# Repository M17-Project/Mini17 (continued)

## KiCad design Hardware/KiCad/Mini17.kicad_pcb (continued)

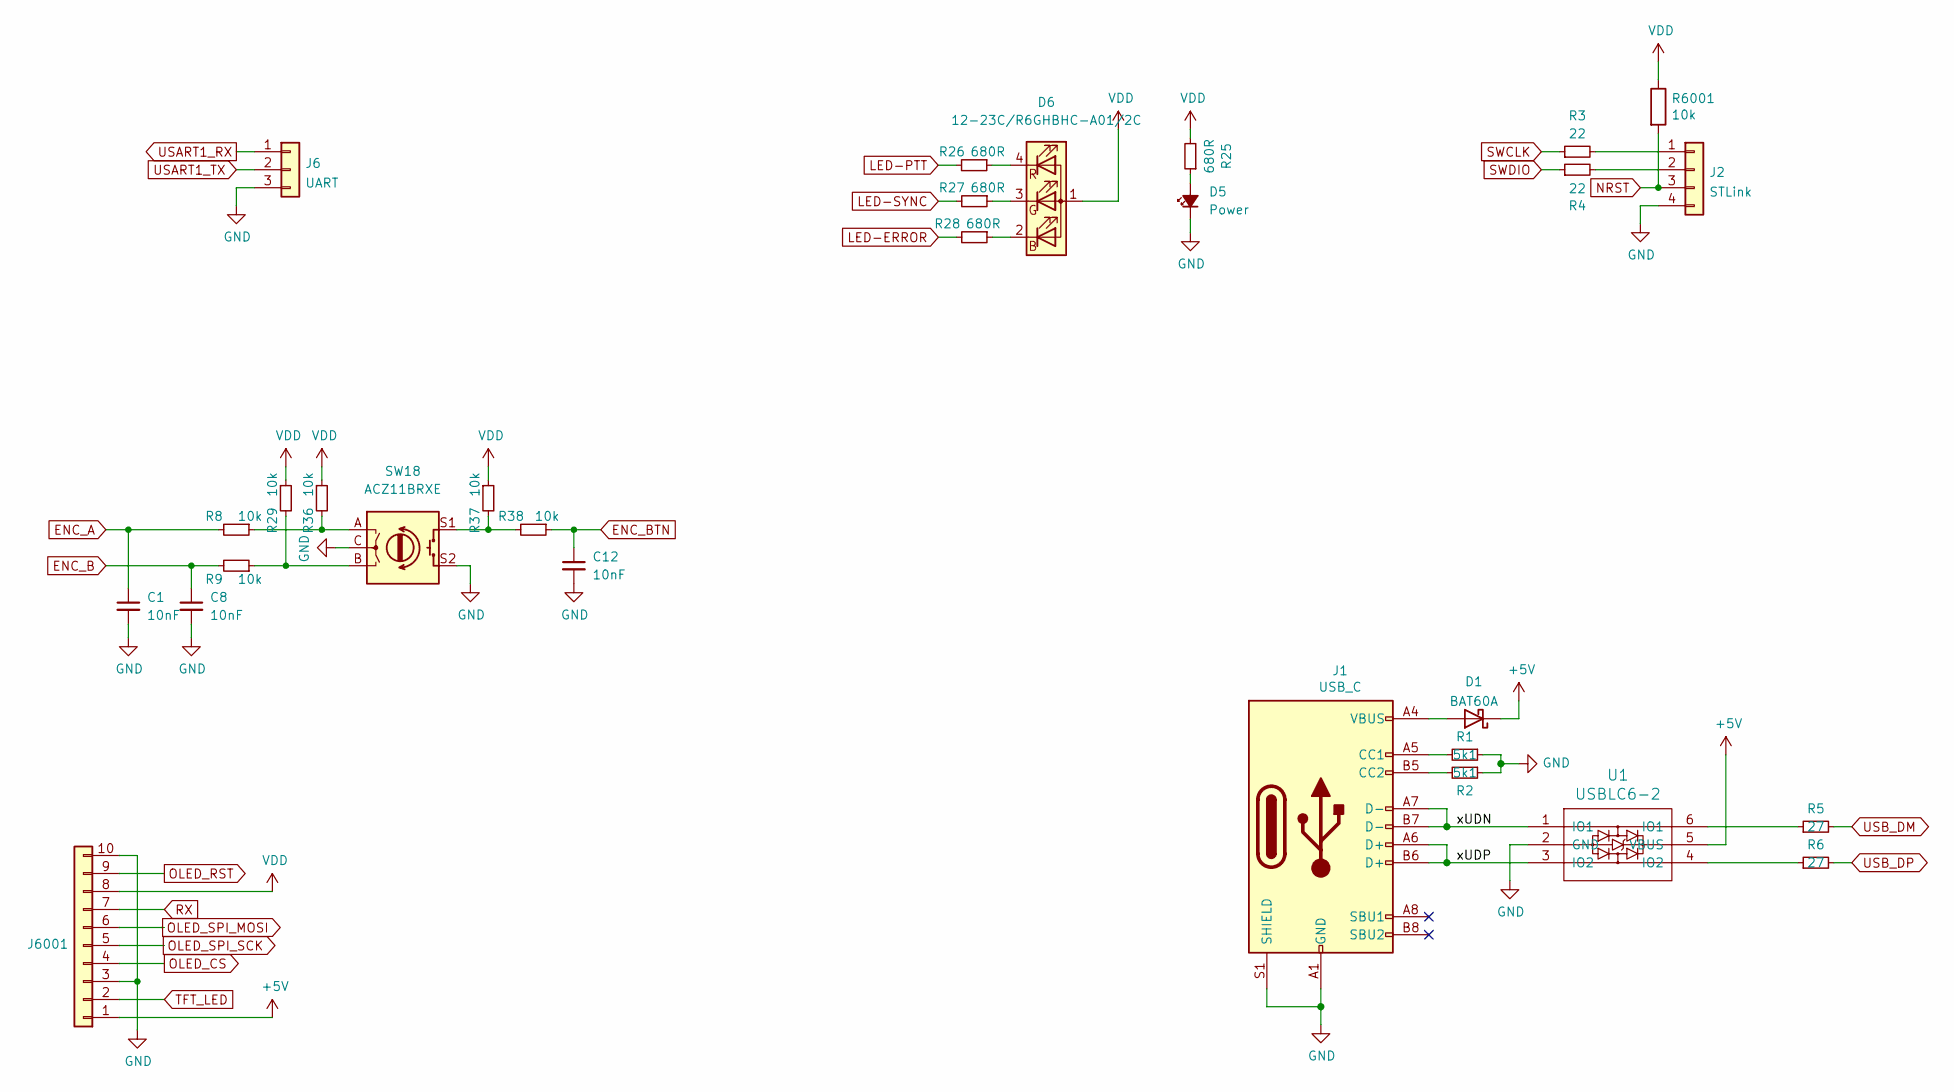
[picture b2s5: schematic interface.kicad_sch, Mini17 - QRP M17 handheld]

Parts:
C1, C8, C12: 10nF; C_0402_1005Metric
D1: BAT60A; D_SOD-323
D5: Power; D_0201_0603Metric
D6: 12-23C/R6GHBHC-A01/2C; LED_RGB_Everlight_EASV3015RGBA0_Horizontal
J1: USB_C; USB_C_Receptacle_GCT_USB4085
J2: STLink; PinHeader_1x04_P2.54mm_Vertical
J6: UART; PinHeader_1x03_P2.54mm_Vertical
J6001: (no value)
R1, R2: 5k1; R_0402_1005Metric
R3, R4: 22; R_0402_1005Metric
R5, R6: 27; R_0402_1005Metric
R8, R9, R29, R36, R37, R38: 10k; R_0402_1005Metric
R25, R26, R27, R28: 680R; R_0402_1005Metric
R6001: 10k; R_0603_1608Metric
SW18: ACZ11BRXE
U1: USBLC6-2; SOT-23-6

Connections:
+5V: D1.1 (K), J6001.1, U1.5 (VBUS); also elsewhere on the board
/Interface/xUDN: J1.A7 (D-), J1.B7 (D-), U1.1 (IO1)
/Interface/xUDP: J1.A6 (D+), J1.B6 (D+), U1.3 (IO2)
ENC_A: C1.1, R8.2; also elsewhere on the board
ENC_B: C8.1, R9.2; also elsewhere on the board
ENC_BTN: C12.1, R38.1; also elsewhere on the board
GND: C1.2, C8.2, C12.2, D5.1 (K), J1.A1 (GND), J1.A12 (GND), J1.B1 (GND), J1.B12 (GND), J1.S1 (SHIELD), J2.4, J6.3, J6001.3, J6001.10, R1.1, R2.1, SW18.C, SW18.S2, U1.2 (GND); also elsewhere on the board
LED-ERROR: R28.2
LED-PTT: R26.2
LED-SYNC: R27.2
NRST: J2.3, R6001.2; also elsewhere on the board
unnamed: D1.2 (A), J1.A4 (VBUS), J1.A9 (VBUS), J1.B4 (VBUS), J1.B9 (VBUS)
unnamed: D5.2 (A), R25.1
unnamed: D6.2 (BK), R28.1
unnamed: D6.3 (GK), R27.1
unnamed: D6.4 (RK), R26.1
unnamed: J1.A5 (CC1), R1.2
unnamed: J1.B5 (CC2), R2.2
unnamed: J2.1, R3.2
unnamed: J2.2, R4.2
unnamed: R5.1, U1.6 (IO1)
unnamed: R6.1, U1.4 (IO2)
unnamed 100: R9.1, R29.2, SW18.B; also elsewhere on the board
unnamed 101: R8.1, R36.2, SW18.A; also elsewhere on the board
unnamed: R37.2, R38.2, SW18.S1
OLED_CS: J6001.4; also elsewhere on the board
OLED_RST: J6001.9; also elsewhere on the board
OLED_SPI_MOSI: J6001.6; also elsewhere on the board
OLED_SPI_SCK: J6001.5; also elsewhere on the board
RX: J6001.7
SWCLK: R3.1; also elsewhere on the board
SWDIO: R4.1; also elsewhere on the board
TFT_LED: J6001.2; also elsewhere on the board
USART1_RX: J6.1; also elsewhere on the board
USART1_TX: J6.2; also elsewhere on the board
USB_DM: R5.2; also elsewhere on the board
USB_DP: R6.2; also elsewhere on the board
VDD: D6.1 (A), J6001.8, R25.2, R29.1, R36.1, R37.1, R6001.1; also elsewhere on the board

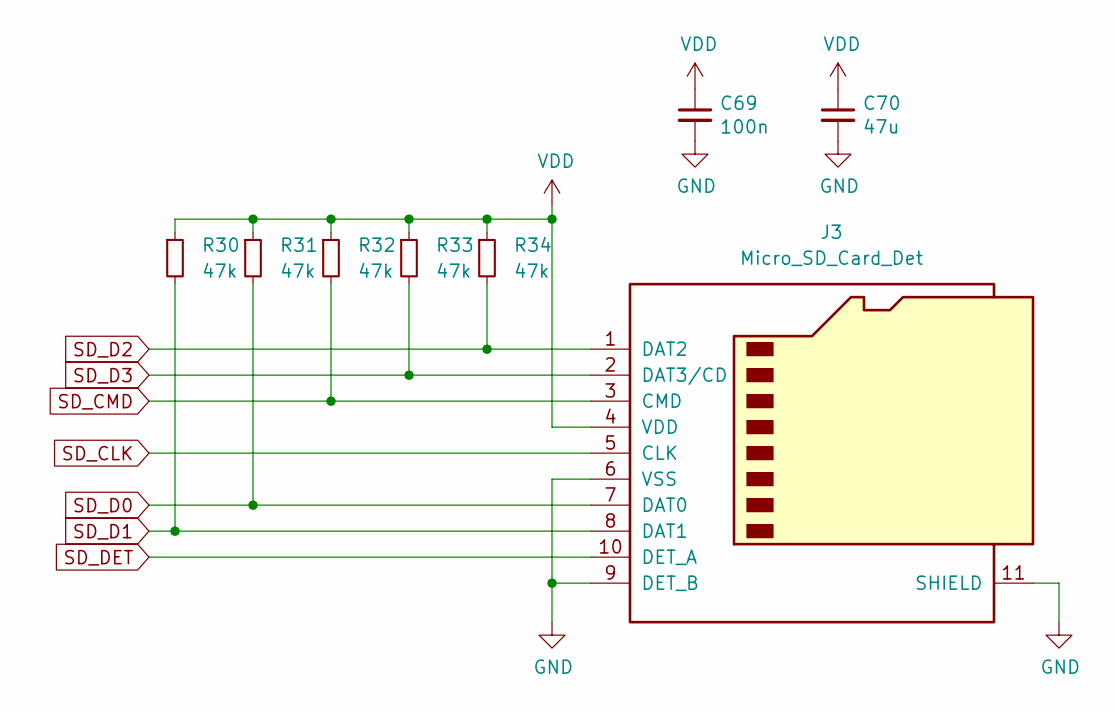
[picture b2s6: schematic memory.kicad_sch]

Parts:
C69: 100n; C_0402_1005Metric
C70: 47u; C_0603
J3: Micro_SD_Card_Det; microSD_HC_Hirose_DM3AT-SF-PEJM5
R30, R31, R32, R33, R34: 47k; R_0402_1005Metric

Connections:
GND: C69.2, C70.2, J3.6 (VSS), J3.9 (DET_B), J3.11 (SHIELD); also elsewhere on the board
SD_CLK: J3.5 (CLK); also elsewhere on the board
SD_CMD: J3.3 (CMD), R32.2; also elsewhere on the board
SD_D0: J3.7 (DAT0), R31.2; also elsewhere on the board
SD_D1: J3.8 (DAT1), R30.2; also elsewhere on the board
SD_D2: J3.1 (DAT2), R34.2; also elsewhere on the board
SD_D3: J3.2 (DAT3/CD), R33.2; also elsewhere on the board
VDD: C69.1, C70.1, J3.4 (VDD), R30.1, R31.1, R32.1, R33.1, R34.1; also elsewhere on the board

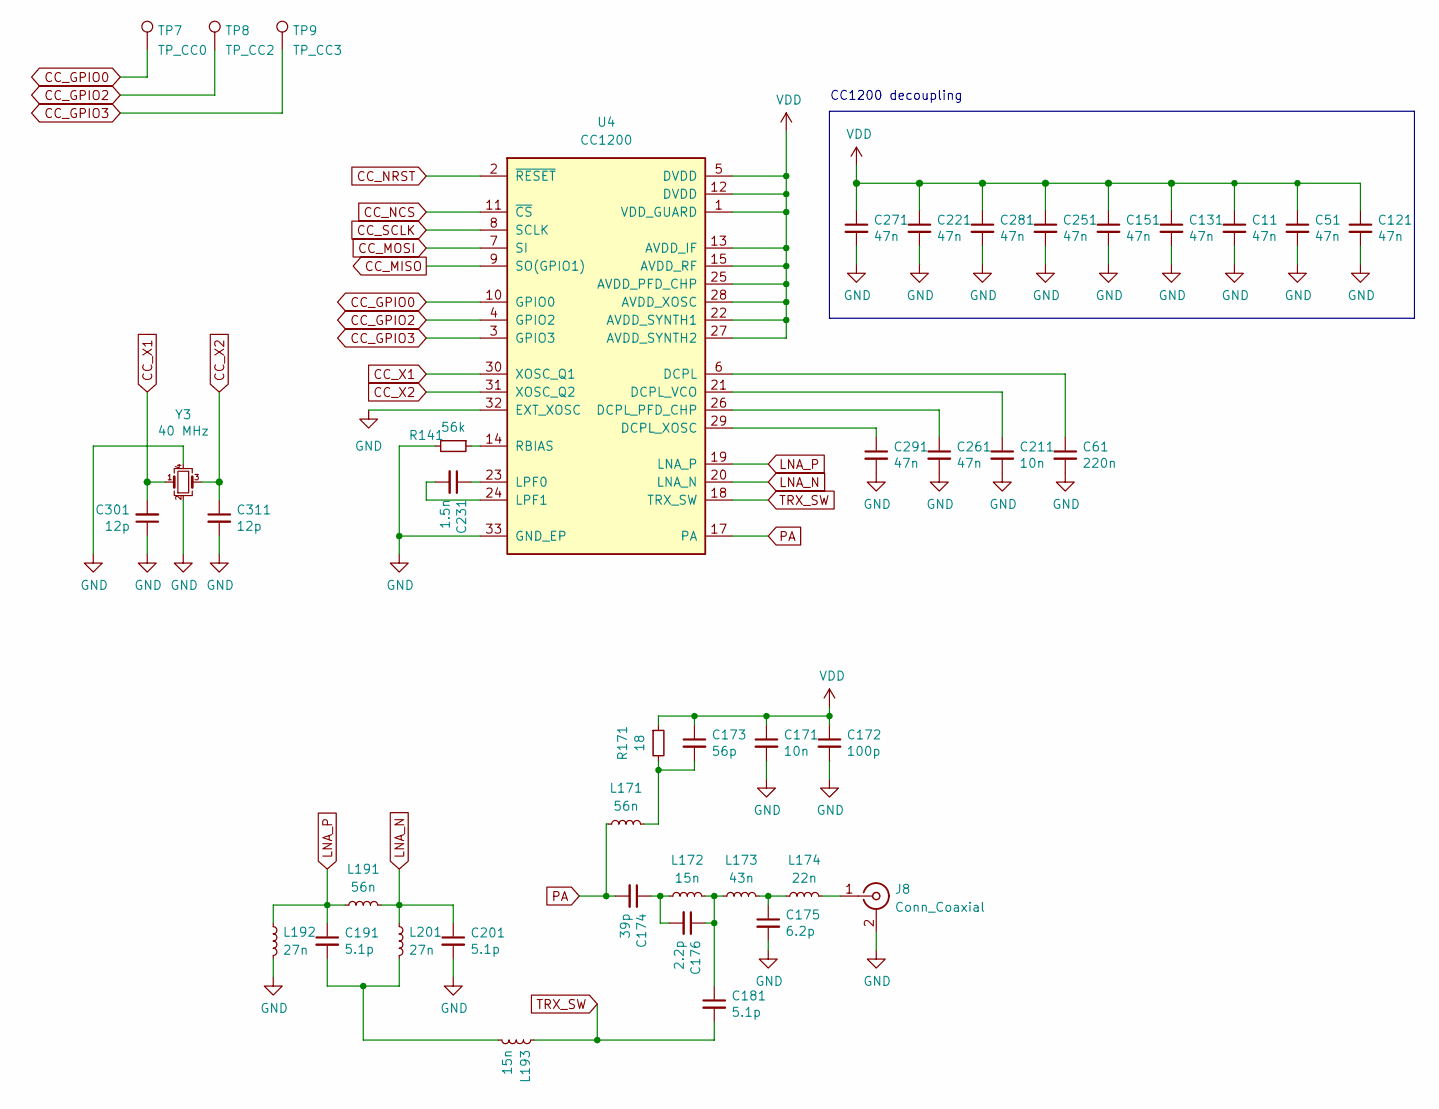
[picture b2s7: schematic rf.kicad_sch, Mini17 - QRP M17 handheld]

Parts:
C11, C51, C121, C131, C151, C221, C251, C261, C271, C281, C291: 47n; C_0402_1005Metric
C61: 220n; C_0402_1005Metric
C171, C211: 10n; C_0402_1005Metric
C172: 100p; C_0402_1005Metric
C173: 56p; C_0402_1005Metric
C174: 39p; C_0402_1005Metric
C175: 6.2p; C_0402_1005Metric
C176: 2.2p; C_0402_1005Metric
C181, C191, C201: 5.1p; C_0402_1005Metric
C231: 1.5n; C_0402_1005Metric
C301, C311: 12p; C_0402_1005Metric
J8: Conn_Coaxial; SMA_Amphenol_901-143_Horizontal
L171, L191: 56n; L_0402_1005Metric
L172, L193: 15n; L_0402_1005Metric
L173: 43n; L_0402_1005Metric
L174: 22n; L_0402_1005Metric
L192, L201: 27n; L_0402_1005Metric
R141: 56k; R_0402_1005Metric
R171: 18; R_0402_1005Metric
TP7: TP_CC0; TestPoint_Pad_D1.0mm
TP8: TP_CC2; TestPoint_Pad_D1.0mm
TP9: TP_CC3; TestPoint_Pad_D1.0mm
U4: CC1200; QFN-32-1EP_5x5mm_P0.5mm_EP3.45x3.45mm
Y3: 40 MHz; Crystal_SMD_3225-4Pin_3.2x2.5mm

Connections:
CC_GPIO0: TP7.1, U4.10 (GPIO0); also elsewhere on the board
CC_GPIO2: TP8.1, U4.4 (GPIO2); also elsewhere on the board
CC_GPIO3: TP9.1, U4.3 (GPIO3); also elsewhere on the board
CC_MISO: U4.9 (SO(GPIO1)); also elsewhere on the board
CC_MOSI: U4.7 (SI); also elsewhere on the board
CC_NCS: U4.11 (~CS); also elsewhere on the board
CC_NRST: U4.2 (~RESET); also elsewhere on the board
CC_SCLK: U4.8 (SCLK); also elsewhere on the board
CC_X1: C301.2, U4.30 (XOSC_Q1), Y3.1
CC_X2: C311.1, U4.31 (XOSC_Q2), Y3.3
GND: C11.2, C51.2, C61.2, C121.2, C131.2, C151.2, C171.2, C172.2, C175.2, C201.2, C211.2, C221.2, C251.2, C261.2, C271.2, C281.2, C291.2, C301.1, C311.2, J8.2 (Ext), L192.2, R141.2, U4.32 (EXT_XOSC), U4.33 (GND_EP), Y3.2, Y3.4; also elsewhere on the board
LNA_N: C201.1, L191.2, L201.1, U4.20 (LNA_N)
LNA_P: C191.1, L191.1, L192.1, U4.19 (LNA_P)
unnamed: C61.1, U4.6 (DCPL)
unnamed: C173.2, L171.2, R171.2
unnamed: C174.1, C176.2, L172.1
unnamed: C175.1, L173.2, L174.1
unnamed: C176.1, C181.1, L172.2, L173.1
unnamed: C191.2, L193.2, L201.2
unnamed: C211.1, U4.21 (DCPL_VCO)
unnamed: C231.1, U4.23 (LPF0)
unnamed: C231.2, U4.24 (LPF1)
unnamed: C261.1, U4.26 (DCPL_PFD_CHP)
unnamed: C291.1, U4.29 (DCPL_XOSC)
unnamed: J8.1 (In), L174.2
unnamed: R141.1, U4.14 (RBIAS)
PA: C174.2, L171.1, U4.17 (PA)
TRX_SW: C181.2, L193.1, U4.18 (TRX_SW)
VDD: C11.1, C51.1, C121.1, C131.1, C151.1, C171.1, C172.1, C173.1, C221.1, C251.1, C271.1, C281.1, R171.1, U4.1 (VDD_GUARD), U4.5 (DVDD), U4.12 (DVDD), U4.13 (AVDD_IF), U4.15 (AVDD_RF), U4.22 (AVDD_SYNTH1), U4.25 (AVDD_PFD_CHP), U4.27 (AVDD_SYNTH2), U4.28 (AVDD_XOSC); also elsewhere on the board

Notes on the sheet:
CC1200 decoupling

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
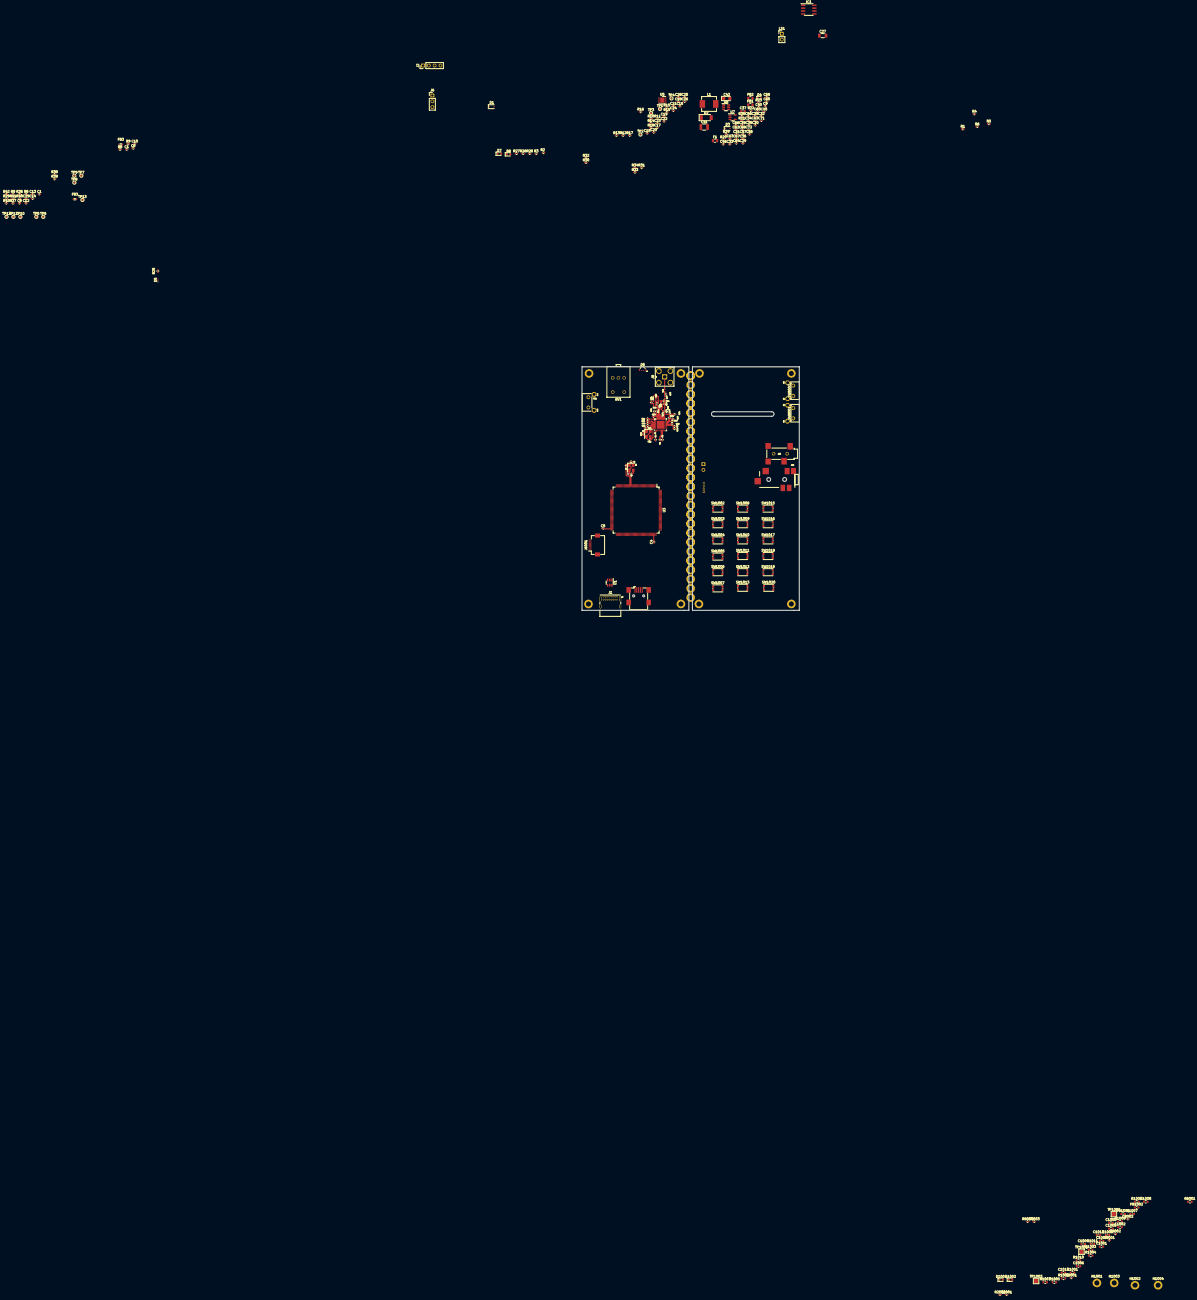
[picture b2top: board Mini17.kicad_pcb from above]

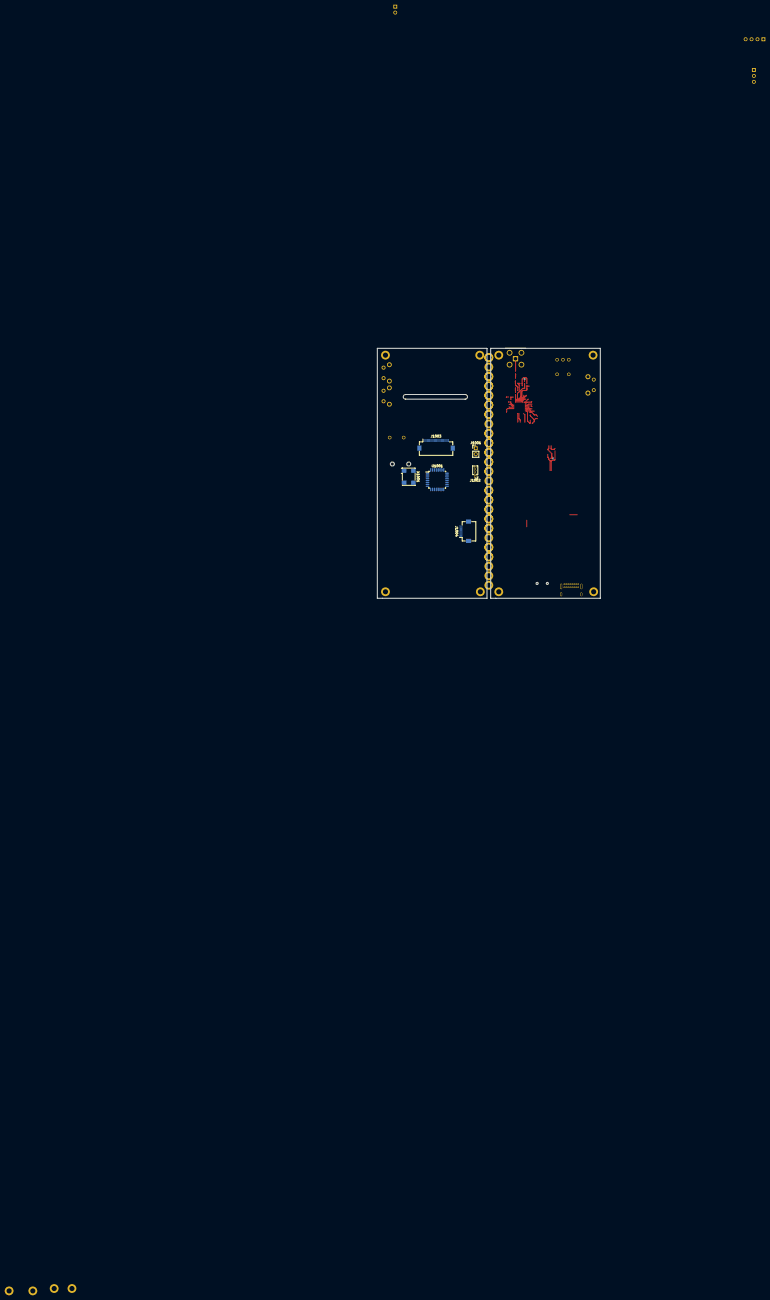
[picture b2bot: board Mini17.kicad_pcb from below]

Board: 4 copper layers, 95.5 x 107.1 mm, 254 parts (6 on the bottom side), 139 nets.

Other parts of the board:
C1#2, C8#2: 10nF; C_0402_1005Metric
C13: 100nF; C_0402_1005Metric
C14, C29: 100n; C_0402_1005Metric
C29#2, C30, C31, C32, C33, C34, C36, C71, C72: 47n; C_0402_1005Metric
D7: Sync; D_0603_1608Metric
D8: Error; D_0603_1608Metric
FB3#2: BLM18AG601SN1D; 0603
J10: MIC_EXT
J12: SPK_EXT
R8#2, R9#2, R40, R41, R42, R43: 10k; R_0402_1005Metric
R39: 47k; R_0402_1005Metric

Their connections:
+5V: J10.1; also elsewhere on the board
BOOT0: C29.1, R43.2; also elsewhere on the board
BTN_F1: C14.1, R41.2; also elsewhere on the board
ENC_A: C1#2.1, R8#2.2; also elsewhere on the board
ENC_B: C8#2.1, R9#2.2; also elsewhere on the board
GND: C1#2.2, C8#2.2, C13.2, C14.2, C29.2, C29#2.2, C30.2, C31.2, C32.2, C33.2, C34.2, C36.2, C71.2, C72.2, J12.2; also elsewhere on the board
MIC: FB3#2.1; also elsewhere on the board
NRST: C13.1, R39.1; also elsewhere on the board
unnamed 85: FB3#2.2; also elsewhere on the board
unnamed 100: R9#2.1; also elsewhere on the board
unnamed 101: R8#2.1; also elsewhere on the board
unnamed: R40.2, R41.1
unnamed: R42.2, R43.1
VDD: C29#2.1, C30.1, C31.1, C32.1, C33.1, C34.1, C36.1, C71.1, C72.1, R40.1, R42.1; also elsewhere on the board

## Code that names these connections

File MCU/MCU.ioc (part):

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Mcu.Name=STM32F427Z(G-I)Tx
Mcu.Package=LQFP144
Mcu.UserName=STM32F427ZGTx
PA0/WKUP.GPIOParameters=GPIO_Label
PA0/WKUP.GPIO_Label=AUDIO_MIC
PA0/WKUP.Signal=ADCx_IN0
PA1.GPIOParameters=GPIO_Label
PA1.GPIO_Label=BAT_MEAS
PA1.Signal=ADCx_IN1
PA10.Mode=Asynchronous
PA10.Signal=USART1_RX
PA11.Mode=Device_Only
PA11.Signal=USB_OTG_FS_DM
PA12.Mode=Device_Only
PA12.Signal=USB_OTG_FS_DP
PA13.Mode=Serial_Wire
PA13.Signal=SYS_JTMS-SWDIO
PA14.Mode=Serial_Wire
PA14.Signal=SYS_JTCK-SWCLK
PA4.GPIOParameters=GPIO_Label
PA4.GPIO_Label=AF_OUT
PA4.Signal=COMP_DAC1_group
PA5.GPIOParameters=GPIO_Label
PA5.GPIO_Label=LED_PTT
PA5.Signal=S_TIM2_CH1_ETR
PA9.Mode=Asynchronous
PA9.Signal=USART1_TX
PB10.GPIOParameters=GPIO_Label
PB10.GPIO_Label=OLED_SPI_SCK
PB10.Mode=TX_Only_Simplex_Unidirect_Master
PB10.Signal=SPI2_SCK
PB11.GPIOParameters=GPIO_Label
PB11.GPIO_Label=OLED_DC
PB11.Signal=GPIO_Output
PB12.GPIOParameters=GPIO_Label
PB12.GPIO_Label=OLED_CS
PB12.Mode=NSS_Signal_Hard_Output
PB12.Signal=SPI2_NSS
PB13.GPIOParameters=GPIO_Label
PB13.GPIO_Label=OLED_RST
PB13.Signal=GPIO_Output
PB15.GPIOParameters=GPIO_Label
PB15.GPIO_Label=OLED_SPI_MOSI
PB15.Mode=TX_Only_Simplex_Unidirect_Master
PB15.Signal=SPI2_MOSI
PC0.GPIOParameters=GPIO_Label
PC0.GPIO_Label=BTN_F1
PC0.Signal=GPXTI0
PC10.Mode=SD_4_bits_Wide_bus
PC10.Signal=SDIO_D2
PC11.Mode=SD_4_bits_Wide_bus
PC11.Signal=SDIO_D3
PC12.Mode=SD_4_bits_Wide_bus
PC12.Signal=SDIO_CK
PC14/OSC32_IN.Mode=LSE-External-Oscillator
PC14/OSC32_IN.Signal=RCC_OSC32_IN
PC15/OSC32_OUT.Mode=LSE-External-Oscillator
PC15/OSC32_OUT.Signal=RCC_OSC32_OUT
PC2.GPIOParameters=GPIO_Label
PC2.GPIO_Label=MIC_GAIN
PC2.Signal=GPIO_Output
PC3.GPIOParameters=GPIO_Label
PC3.GPIO_Label=MIC_MUTE
PC3.Signal=GPIO_Output
PC6.GPIOParameters=GPIO_Label
PC6.GPIO_Label=ENC_B
PC6.Signal=S_TIM8_CH1
PC7.GPIOParameters=GPIO_Label
PC7.GPIO_Label=ENC_A
PC7.Signal=S_TIM8_CH2
PC8.Mode=SD_4_bits_Wide_bus
PC8.Signal=SDIO_D0
PC9.Mode=SD_4_bits_Wide_bus
PC9.Signal=SDIO_D1
PD12.GPIOParameters=GPIO_Label
PD12.GPIO_Label=LED_ERROR
PD12.Signal=S_TIM4_CH1
PD2.Mode=SD_4_bits_Wide_bus
PD2.Signal=SDIO_CMD
PE5.GPIOParameters=GPIO_Label
PE5.GPIO_Label=LED_SYNC
PE5.Signal=S_TIM9_CH1
PE7.GPIOParameters=GPIO_Label
PE7.GPIO_Label=KP_C2
PE7.Signal=GPXTI7
PE8.GPIOParameters=GPIO_Label
PE8.GPIO_Label=KP_C3
PE8.Signal=GPXTI8
PE9.GPIOParameters=GPIO_Label
PE9.GPIO_Label=KP_C4
PE9.Signal=GPXTI9
PF10.GPIOParameters=GPIO_Label
PF10.GPIO_Label=BTN_F2
PF10.Signal=GPXTI10
PF13.GPIOParameters=GPIO_Label
PF13.GPIO_Label=KP_R4
PF13.Signal=GPXTI13
PF14.GPIOParameters=GPIO_Label
PF14.GPIO_Label=KP_R3
PF14.Signal=GPXTI14
PF15.GPIOParameters=GPIO_Label
PF15.GPIO_Label=KP_R2
PF15.Signal=GPXTI15
PF5.GPIOParameters=GPIO_Label
PF5.GPIO_Label=CC_NRST
PF5.Signal=GPIO_Output
PF6.GPIOParameters=GPIO_Label
PF6.GPIO_Label=CC_NSS
PF6.Mode=NSS_Signal_Hard_Output
PF6.Signal=SPI5_NSS
PF7.GPIOParameters=GPIO_Label
PF7.GPIO_Label=CC_SCLK
PF7.Mode=Full_Duplex_Master
PF7.Signal=SPI5_SCK
PF8.GPIOParameters=GPIO_Label
PF8.GPIO_Label=CC_MISO
PF8.Mode=Full_Duplex_Master
PF8.Signal=SPI5_MISO
PF9.GPIOParameters=GPIO_Label
PF9.GPIO_Label=CC_MOSI
PF9.Mode=Full_Duplex_Master
PF9.Signal=SPI5_MOSI
PG1.GPIOParameters=GPIO_Label
PG1.GPIO_Label=KP_C1
PG1.Signal=GPXTI1
PG12.GPIOParameters=GPIO_Label
PG12.GPIO_Label=CC_GPIO3
PG12.Signal=GPXTI12
PH0/OSC_IN.Mode=HSE-External-Oscillator
PH0/OSC_IN.Signal=RCC_OSC_IN
PH1/OSC_OUT.Mode=HSE-External-Oscillator
PH1/OSC_OUT.Signal=RCC_OSC_OUT
RCC.HSE_VALUE=8000000
RCC.SYSCLKFreq_VALUE=108000000
RCC.SYSCLKSource=RCC_SYSCLKSOURCE_PLLCLK
board=custom

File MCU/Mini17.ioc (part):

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Mcu.Name=STM32F405RGTx
Mcu.Package=LQFP64
Mcu.UserName=STM32F405RGTx
PA0-WKUP.GPIOParameters=GPIO_Label
PA0-WKUP.GPIO_Label=AUDIO_MIC
PA0-WKUP.Signal=ADCx_IN0
PA1.GPIOParameters=GPIO_Label
PA1.GPIO_Label=BAT_MEAS
PA1.Signal=ADCx_IN1
PA10.Mode=Asynchronous
PA10.Signal=USART1_RX
PA11.Mode=Device_Only
PA11.Signal=USB_OTG_FS_DM
PA12.Mode=Device_Only
PA12.Signal=USB_OTG_FS_DP
PA13.Mode=Serial_Wire
PA13.Signal=SYS_JTMS-SWDIO
PA14.Mode=Serial_Wire
PA14.Signal=SYS_JTCK-SWCLK
PA2.GPIOParameters=GPIO_Label
PA2.GPIO_Label=TP_B
PA2.Signal=GPIO_Output
PA3.GPIOParameters=GPIO_Label
PA3.GPIO_Label=CC_GPIO0
PA3.Signal=GPIO_Input
PA4.GPIOParameters=GPIO_Label
PA4.GPIO_Label=AF_OUT
PA4.Signal=COMP_DAC1_group
PA5.GPIOParameters=GPIO_Label
PA5.GPIO_Label=CC_GPIO2
PA5.Signal=GPIO_Input
PA6.GPIOParameters=GPIO_Label
PA6.GPIO_Label=LED_R
PA6.Signal=S_TIM3_CH1
PA7.GPIOParameters=GPIO_Label
PA7.GPIO_Label=LED_G
PA7.Signal=S_TIM3_CH2
PA9.Mode=Asynchronous
PA9.Signal=USART1_TX
PB0.GPIOParameters=GPIO_Label
PB0.GPIO_Label=LED_B
PB0.Signal=S_TIM3_CH3
PB1.GPIOParameters=GPIO_Label
PB1.GPIO_Label=CC_GPIO3
PB1.Signal=GPIO_Input
PB10.Mode=Full_Duplex_Master
PB10.Signal=SPI2_SCK
PB11.GPIOParameters=GPIO_Label
PB11.GPIO_Label=OLED_DC
PB11.Signal=GPIO_Output
PB12.GPIOParameters=GPIO_Label
PB12.GPIO_Label=OLED_CS
PB12.Signal=GPIO_Output
PB13.GPIOParameters=GPIO_Label
PB13.GPIO_Label=KBD_CS
PB13.Signal=GPIO_Output
PB14.Mode=Full_Duplex_Master
PB14.Signal=SPI2_MISO
PB15.Mode=Full_Duplex_Master
PB15.Signal=SPI2_MOSI
PB3.Mode=Full_Duplex_Master
PB3.Signal=SPI1_SCK
PB4.Mode=Full_Duplex_Master
PB4.Signal=SPI1_MISO
PB5.Mode=Full_Duplex_Master
PB5.Signal=SPI1_MOSI
PB6.GPIOParameters=GPIO_Label
PB6.GPIO_Label=SPI1_CS
PB6.Signal=GPIO_Output
PB7.GPIOParameters=GPIO_Label
PB7.GPIO_Label=SPI1_RST
PB7.Signal=GPIO_Output
PB8.GPIOParameters=GPIO_Label
PB8.GPIO_Label=MIC_GAIN
PB8.Signal=GPIO_Output
PB9.GPIOParameters=GPIO_Label
PB9.GPIO_Label=MIC_MUTE
PB9.Signal=GPIO_Output
PC0.GPIOParameters=GPIO_Label
PC0.GPIO_Label=PTT_IN
PC0.Signal=GPXTI0
PC1.GPIOParameters=GPIO_Label
PC1.GPIO_Label=BTN_F1
PC1.Signal=GPXTI1
PC10.Mode=SD_4_bits_Wide_bus
PC10.Signal=SDIO_D2
PC11.Mode=SD_4_bits_Wide_bus
PC11.Signal=SDIO_D3
PC12.Mode=SD_4_bits_Wide_bus
PC12.Signal=SDIO_CK
PC13-ANTI_TAMP.GPIOParameters=GPIO_Label
PC13-ANTI_TAMP.GPIO_Label=TP_A
PC13-ANTI_TAMP.Signal=GPIO_Output
PC2.GPIOParameters=GPIO_Label
PC2.GPIO_Label=BTN_F2
PC2.Signal=GPXTI2
PC3.GPIOParameters=GPIO_Label
PC3.GPIO_Label=ENC_A
PC3.Signal=GPXTI3
PC4.GPIOParameters=GPIO_Label
PC4.GPIO_Label=ENC_B
PC4.Signal=GPXTI4
PC5.GPIOParameters=GPIO_Label
PC5.GPIO_Label=ENC_BTN
PC5.Signal=GPXTI5
PC6.GPIOParameters=GPIO_Label
PC6.GPIO_Label=OLED_RST
PC6.Signal=GPIO_Output
PC7.GPIOParameters=GPIO_Label
PC7.GPIO_Label=SD_DET
PC7.Signal=GPXTI7
PC8.Mode=SD_4_bits_Wide_bus
PC8.Signal=SDIO_D0
PC9.Mode=SD_4_bits_Wide_bus
PC9.Signal=SDIO_D1
PD2.Mode=SD_4_bits_Wide_bus
PD2.Signal=SDIO_CMD
PH0-OSC_IN.Mode=HSE-External-Oscillator
PH0-OSC_IN.Signal=RCC_OSC_IN
PH1-OSC_OUT.Mode=HSE-External-Oscillator
PH1-OSC_OUT.Signal=RCC_OSC_OUT
RCC.HSE_VALUE=8000000
RCC.SYSCLKFreq_VALUE=168000000
RCC.SYSCLKSource=RCC_SYSCLKSOURCE_PLLCLK
board=custom

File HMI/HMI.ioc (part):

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Mcu.Name=STM32F030K6Tx
Mcu.Package=LQFP32
Mcu.UserName=STM32F030K6Tx
PA0.GPIOParameters=GPIO_Label
PA0.GPIO_Label=C1
PA0.Signal=GPXTI0
PA1.GPIOParameters=GPIO_Label
PA1.GPIO_Label=C2
PA1.Signal=GPXTI1
PA10.GPIOParameters=GPIO_Label
PA10.GPIO_Label=F1
PA10.Signal=GPXTI10
PA11.GPIOParameters=GPIO_Label
PA11.GPIO_Label=F2
PA11.Signal=GPXTI11
PA13.Mode=Serial_Wire
PA13.Signal=SYS_SWDIO
PA14.Mode=Serial_Wire
PA14.Signal=SYS_SWCLK
PA2.Mode=Half_duplex(single_wire_mode)
PA2.Signal=USART1_TX
PA3.GPIOParameters=GPIO_Label
PA3.GPIO_Label=C3
PA3.Signal=GPXTI3
PA4.GPIOParameters=GPIO_Label
PA4.GPIO_Label=R1
PA4.Signal=GPXTI4
PA5.GPIOParameters=GPIO_Label
PA5.GPIO_Label=R2
PA5.Signal=GPXTI5
PA6.GPIOParameters=GPIO_Label
PA6.GPIO_Label=R3
PA6.Signal=GPXTI6
PA7.GPIOParameters=GPIO_Label
PA7.GPIO_Label=R4
PA7.Signal=GPXTI7
PA8.GPIOParameters=GPIO_Label
PA8.GPIO_Label=R5
PA8.Signal=GPXTI8
PA9.GPIOParameters=GPIO_Label
PA9.GPIO_Label=R6
PA9.Signal=GPXTI9
PF0-OSC_IN.Mode=HSE-External-Clock-Source
PF0-OSC_IN.Signal=RCC_OSC_IN
board=custom

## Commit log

2022-07-26 Organize things into folders
2022-07-26 README.md badges
2022-07-26 Add twitter (What about mastodon?)
2022-07-27 RF part update
2022-07-27 Organize schematics into folders V2
2022-07-27 Add 4x4 keyboard
2022-07-28 Decoupling capacitors
2022-07-29 Add decoupling capacitors and fix issue #7
2022-07-29 Added footprints for decoupling caps
2022-07-29 PDF render
2022-07-29 Initial PCB arrangement
2022-07-31 Connected SD card to the micro
2022-07-31 Update
    - `H*` holes changed to M2
    - RTC battery was connected to `VDDA` instead of `VDD`
    - added CC1200 decoupling caps
2022-07-31 Added some connections
2022-08-03 Add USB and keypad connections
2022-08-03 Use standard notation for USB lines and fix label types
2022-08-04 Add no connection labels, anotate schematic, regen pdf and create netlist
2022-08-05 add MCU pinouts & add STM .ioc file
2022-08-05 adjust footprints
2022-08-06 move cc1200 spi to spi-5 & update other labels throughout
2022-08-06 update .ioc file to latest version
2022-08-06 starting basic layout
2022-08-07 rough layout of cc1200
2022-08-07 fix issue 21 & 20 & move MCU to align w/ grid
2022-08-07 add pdf schematic
2022-08-07 R7 update
2022-08-07 Use a single RGB LED
2022-08-07 fixup PTT/Audio (Issue 14), add RGB LED (Issue 26), Connect LEDs to MCU & add them to the .ioc file
2022-08-08 add encoder & volume control, move SD_DET to accommodate encoder
2022-08-08 Minor corrections
    - fixed microphone connection and part values
    - added a few TPs
    - changed C27 footprint
2022-08-08 Pinout fix/update
2022-08-08 Schematic update
    - nets for the internal speaker renamed
    - encoder nets renamed, encoder circuit updated
    - various other minor edits
2022-08-08 Additional function buttons - F1, F2
    Closes #24
2022-08-08 Schematic update - PDF render
2022-08-08 Pinout update
    Added `BTN_F1` and `BTN_F2` function buttons
2022-08-10 add fpc display board connector, move components around, rough size of board
2022-08-15 many edits throughout, added board edges for main & HMI combined, added rough layouts for some components on both
2022-08-15 J3 UART conn change
    Fixes #33
2022-08-16 SPI for keyboard readout, FPC conn update
2022-08-16 MCU swap
2022-08-16 Removed RTC
2022-08-17 add HMI J4 and encoder footprints and change encoder schematic
2022-08-19 Add ANY_KEY signal from keypad.
2026-01-30 Update Mini17 description in README.md
    Stalled.
